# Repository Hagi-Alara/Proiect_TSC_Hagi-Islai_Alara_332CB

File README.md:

# InkTime - Open Source Smartwatch

Prezentul repository include documentația tehnică și fișierele de proiectare hardware (stadiul EVT - Engineering Verification Test) pentru proiectul InkTime. Acesta reprezintă un smartwatch open-source, având la bază microcontrolerul nRF52840. Proiectul acoperă întregul ciclu de dezvoltare hardware: specificații, schemă electrică, proiectare PCB și integrare mecanică.

## Descrierea Funcționalității Hardware

Sistemul este arhitecturat în jurul SoC-ului nRF52840, selectat pentru suportul Bluetooth Low Energy (BLE) și eficiența energetică ridicată.

**Module și Interfețe Integrate:**
* **Display E-Paper:** Interfațat prin protocolul SPI, garantând un consum energetic minim (curent absorbit exclusiv în timpul actualizării ecranului).
* **Unitate de Măsură Inerțială (IMU):** Utilizată pentru detectarea gesturilor. Comunicarea se realizează exclusiv prin magistrala I2C.
* **Feedback Haptic:** Motor de vibrații controlat printr-un circuit integrat (driver) dedicat, implementat pentru notificări.
* **Interfață Utilizator:** Trei butoane fizice cu acționare tactilă, configurate cu rezistențe de pull-up interne.
* **Managementul Energiei:** Sistemul este alimentat printr-un acumulator Li-Po conectat direct la pad-urile circuitului imprimat, eliminând conectorul JST pentru a respecta limitările de gabarit pe axa Z. Încărcarea se realizează prin intermediul interfeței USB-C, gestionată de un circuit integrat de management al puterii (PMIC), în timp ce nivelul de încărcare este monitorizat de un Fuel Gauge.

## Bill of Materials (BOM) Principal

| Componentă | Pachet / Capsulă | Funcție |
| :--- | :--- | :--- |
| **nRF52840-QIAA** | aQFN-73 | Microcontroler principal (SoC) + BLE |
| **BMA421** | LGA-12 | IMU (Accelerometru pentru gesturi) |
| **BQ25180** | DSBGA | PMIC (Management Încărcare Baterie) |
| **MAX17048** | TDFN-8 | Fuel Gauge (Monitorizare nivel baterie) |
| **DRV2605** | BGA-9 | Driver Haptic pentru motorul de vibrații |
| **RT6160A** | WLCSP | Regulator DC/DC (Buck-Boost pentru 3.3V) |
| **Conector Molex** | FPC 24-pin 0.5mm | Conector pentru Display E-Paper |

## Maparea Pinilor (nRF52840)

Alocarea pinilor a fost optimizată pentru a minimiza încrucișările de trasee pe cablajul imprimat.

| Pin nRF52840 | Nume Rețea | Interfață / Funcție |
| :--- | :--- | :--- |
| **P$AD10, P$K2, P$AD12** | `EPD_DC`, `EPD_CS`, `EPD_RST` | Control E-Paper (Data/Command, Chip Select, Reset) |
| **P$P13, P$A12** | `MOSI`, `SCK` | SPI Date & Clock pentru afișaj |
| **P$AD12** | `EPD_BUSY` | Status E-Paper (Indicator de ocupare) |
| **P$L1, P$M2** | `SDA`, `SCL` | I2C Date & Clock (PMIC, Fuel Gauge, IMU) |
| **P$AD8, P$AC9, P$W24** | `P0.13`, `P0.14`, `P1.02` | Butoane interfață utilizator (Up, Enter, Down) |
| **P$AD6, P$AD4, P$AD2**| `D+`, `D-`, `VBUS` | USB-C ESD Protection & VBUS Detect |
| **P$U1** | `HAPTIC_EN` | Semnal de activare Driver Haptic |
| **P$T2** | `PMIC_INT` | Întrerupere Baterie Li-Po |
| **P$N1, P$P2** | `IMU_INT1`, `IMU_INT2` | Întreruperi IMU |
| **P$J24** | `ALERT` | Alertă Fuel Gauge |
| **P$AD22, P$AA24, P$AC24** | `SWO`, `SWDCLK`, `SWDIO`| Interfață de depanare (SWD) |
| **P$AC13** | `RESET` | Semnal Hardware Reset |
| **P$Y23** | `P1.01` | Control E-Paper Drive Circuit |

## Randări 3D

## Etape de Implementare

1. **Definirea Specificațiilor și a Componentelor:** Selectarea componentelor necesare respectând cerința unui consum redus de energie (ultra-low-power).
2. **Proiectarea Schemei Electrice (Validare ERC):** Interconectarea subsistemelor de alimentare (PMIC, LDO), logică digitală (I2C, SPI) și radiofrecvență (RF).
3. **Proiectarea Cablajului Imprimat (Validare DRC):** * Amplasarea componentelor respectând constrângerile mecanice ale carcasei.
   * Rutarea traseelor de impedanță controlată pentru antena BLE, cu implementarea zonelor de restricție (Keepout) pe toate straturile.
   * Generarea planurilor de masă (Polygon Pours) pe straturile Top și Bottom.
4. **Validarea Mecanică:** Exportul ansamblului în format 3D STEP pentru verificarea toleranțelor de integrare în carcasa fizică.

## Erori de Proiectare (DRC/ERC) și Decizii de Inginerie Asumate

În urma procesului de verificare automată a regulilor de proiectare și a schemelor electrice (DRC/ERC), au fost raportate o serie de avertismente. Acestea au fost analizate și acceptate intenționat, având la bază următoarele justificări tehnice:

* **Erori ERC: "POWER pin connected to..." (Exemplu: U1 VDD connected to 3V3)**
  * *Justificare:* Aceste avertismente au fost ignorate. Cauza constă în definirea generică a pinilor de alimentare în biblioteca software (ex. "VDD"), în timp ce în schema proiectului rețeaua poartă o denumire specifică ("3V3" sau "VBAT"). Conexiunile sunt corecte din punct de vedere electric.
* **Erori ERC: "Only one pin on net" (Exemplu: SWO, SDA/1.4C, P1.15)**
  * *Justificare:* Aceste erori au fost ignorate. Avertismentele sunt generate deoarece pinii respectivi au fost rutați exclusiv către puncte de test (Test Points) pentru depanare sau au fost etichetați pentru funcționalități viitoare, nefiind conectați la un alt circuit integrat. Prezența lor este necesară pentru testarea hardware.
* **Erori DRC: "Overlap", "Solder mask", "Pad ct Top"**
  * *Justificare:* Aceste erori au fost acceptate. Având în vedere densitatea ridicată a plăcii, toleranțele măștii de lipire (Solder Mask) pentru componentele cu pas foarte mic (cum este conectorul FPC) se suprapun la nivelul software-ului CAD. Aceste deviații se încadrează în capabilitățile și toleranțele standard ale producătorului de cablaje imprimate.
* **Erori DRC: "Board Outline / Copper Clearance"**
  * *Justificare:* Aceste erori au fost acceptate. Erorile sunt provocate de componentele amplasate la limita cablajului (conectorul USB-C, contactele bateriei). Din rațiuni de asamblare mecanică, pinii de susținere și portul trebuie să se intersecteze cu conturul fizic al plăcii (Board Outline). Deși programul raportează o încălcare a regulilor de distanță, implementarea corespunde cerințelor fizice de funcționare.

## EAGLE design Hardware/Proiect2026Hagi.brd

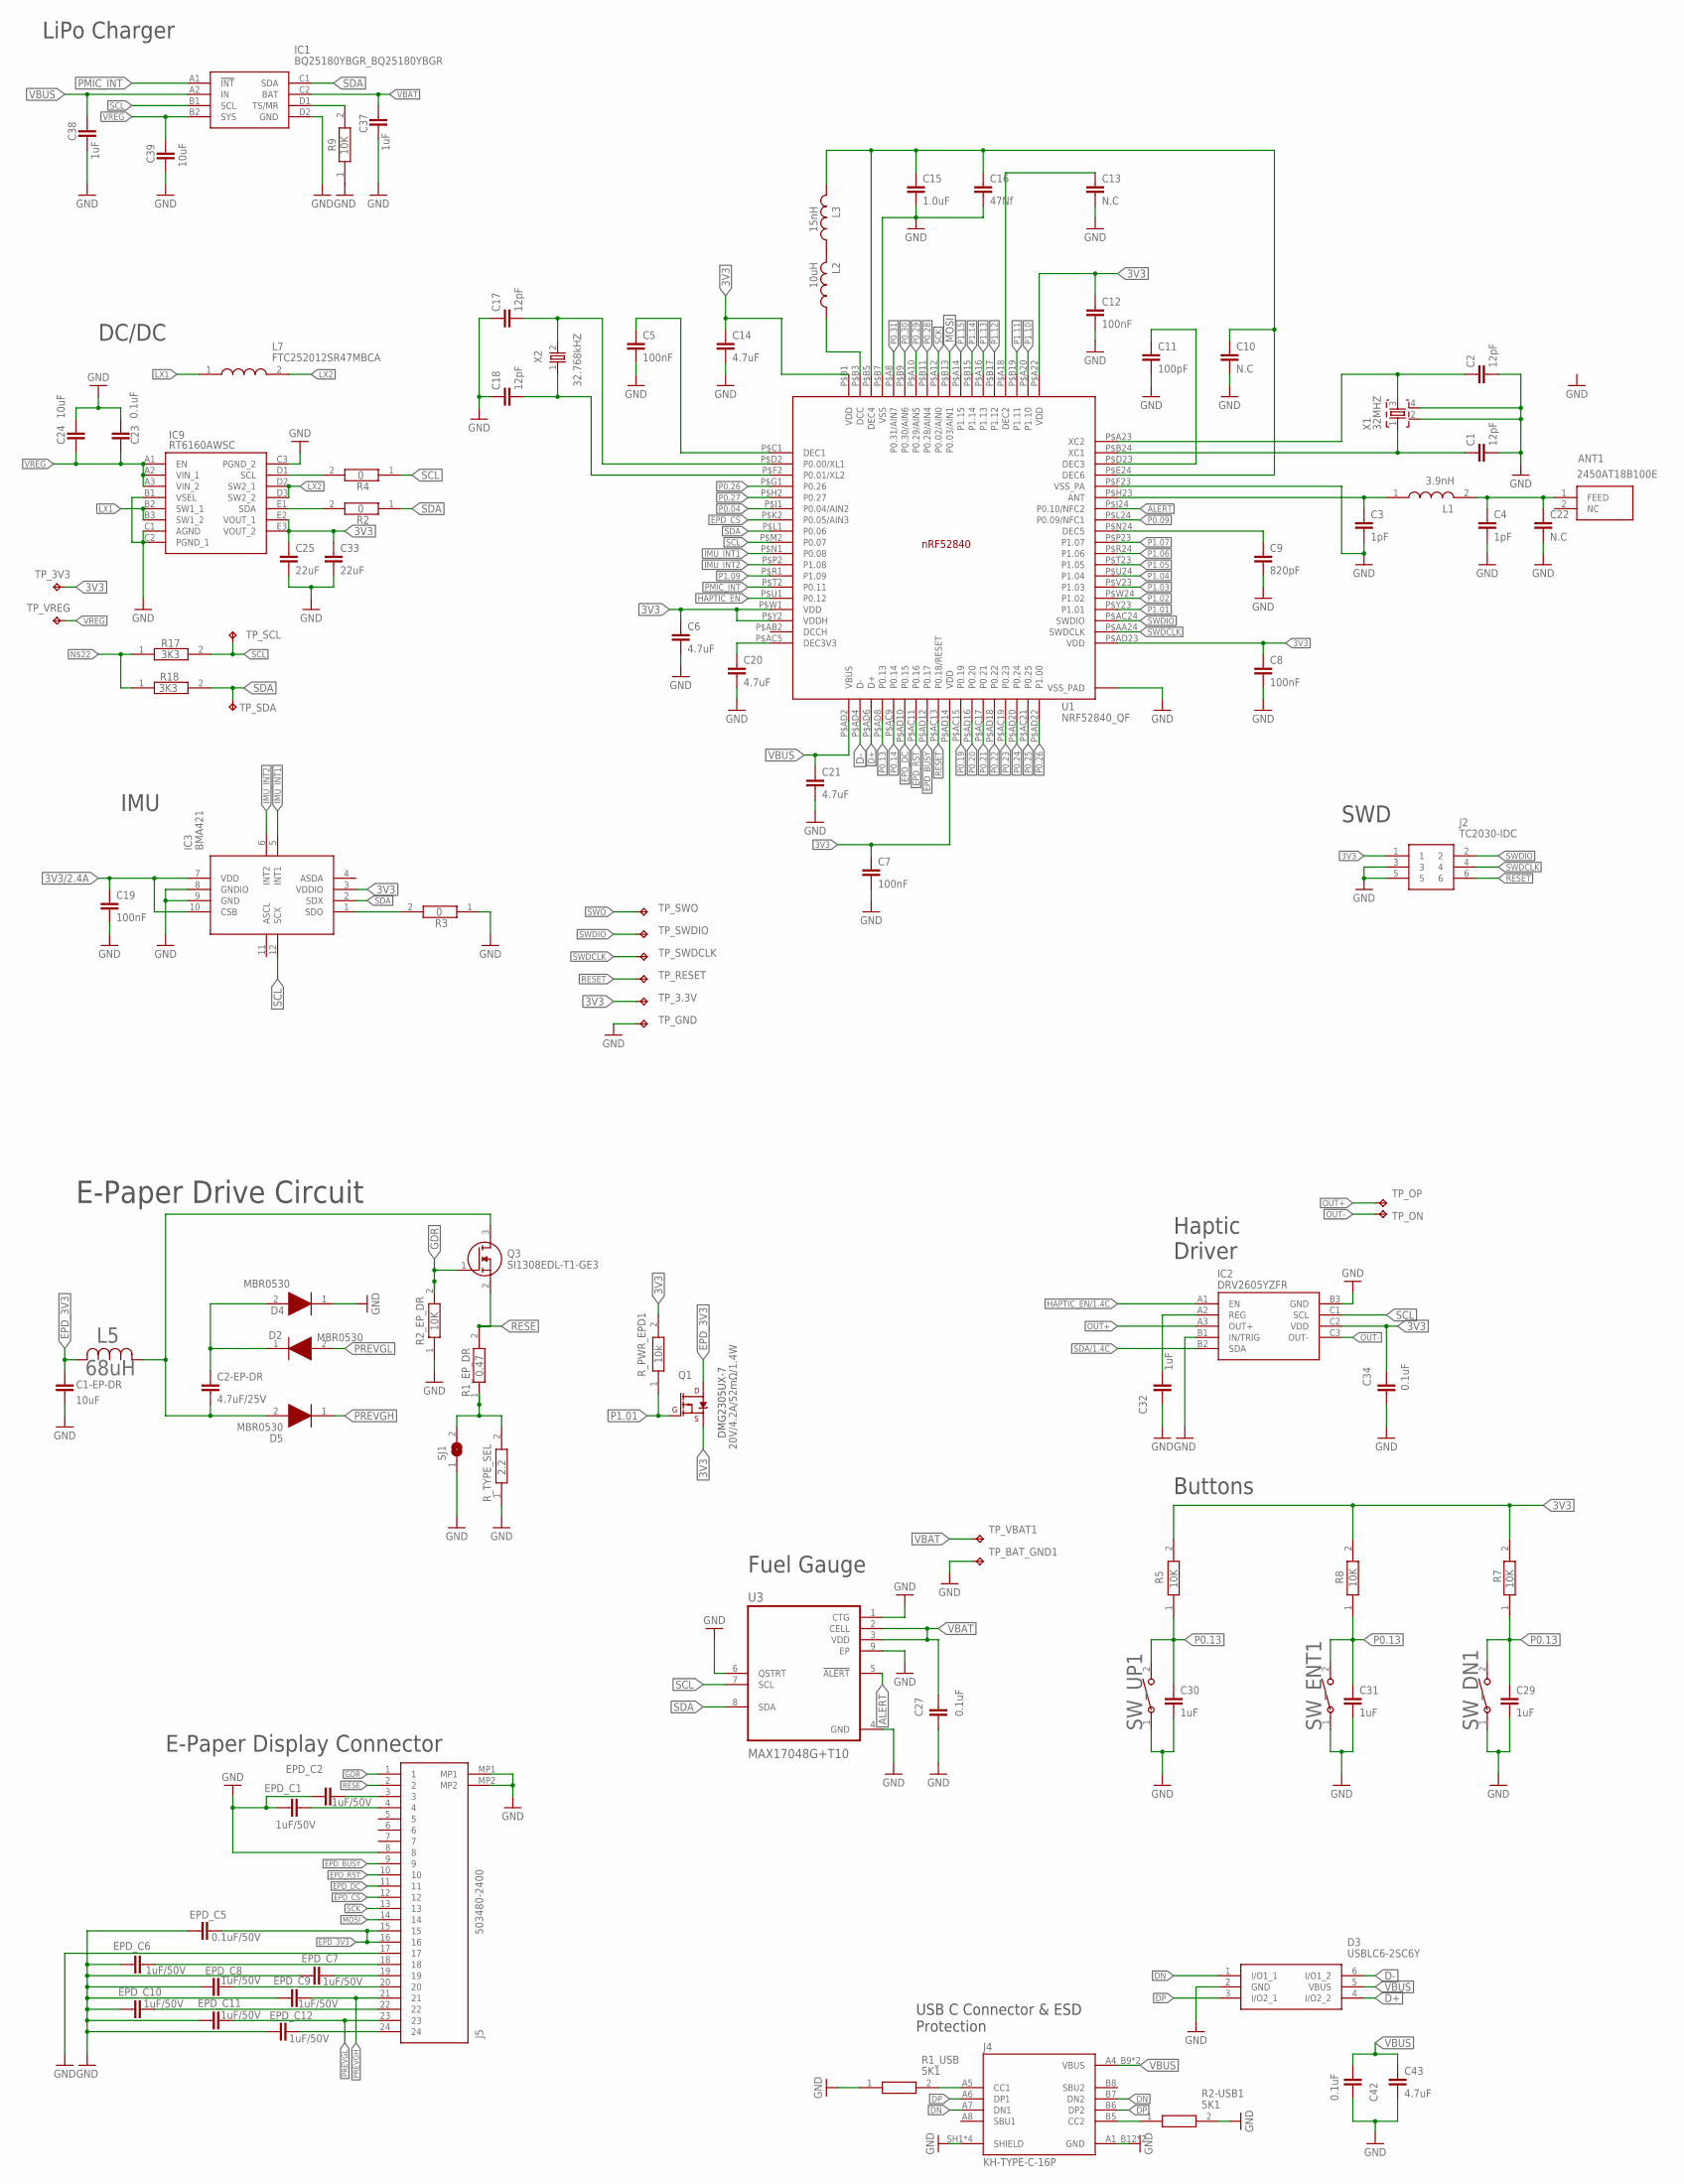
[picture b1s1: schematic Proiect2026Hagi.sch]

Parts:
ANT1: 2450AT18B100E; 2450AT18B100E_ANTC3216X140N
C1, C2, C17, C18: 12pF; NORDIC_NRF_3_RESC0201_L
C1-EP-DR: 10uF; NORDIC_NRF_3_RESC0402_L
C2-EP-DR: 4.7uF/25V; NORDIC_NRF_3_RESC0402_L
C3, C4: 1pF; NORDIC_NRF_3_RESC0201_L
C5, C7, C8, C12, C19: 100nF; NORDIC_NRF_3_RESC0201_L
C6, C14, C20, C21, C43: 4.7uF; NORDIC_NRF_3_RESC0402_L
C9: 820pF; NORDIC_NRF_3_RESC0201_L
C10, C13, C22: N.C; NORDIC_NRF_3_RESC0201_L
C11: 100pF; NORDIC_NRF_3_RESC0201_L
C15: 1.0uF; NORDIC_NRF_3_RESC0402_L
C16: 47Nf; NORDIC_NRF_3_RESC0201_L
C23: 0.1uF; NORDIC_NRF_3_RESC0402_L
C24: 10uF; NORDIC_NRF_3_RESC0201_L
C25, C33: 22uF; NORDIC_NRF_3_RESC0402_L
C27, C34, C42: 0.1uF; NORDIC_NRF_3_RESC0201_L
C29, C30, C31, C32: 1uF; NORDIC_NRF_3_RESC0402_L
C37, C38: 1uF; PERFECT_0402_0402
C39: 10uF; PERFECT_0402_0402
D2, D4, D5: MBR0530; ESP32_C6_LIBRARY_5_SOD3716X135N
D3: USBLC6-2SC6Y; ESP32_C6_LIBRARY_3_SOT95P280X145-6N
EPD_C1, EPD_C2, EPD_C6, EPD_C7, EPD_C8, EPD_C9, EPD_C10, EPD_C11, EPD_C12: 1uF/50V; NORDIC_NRF_3_RESC0402_L
EPD_C5: 0.1uF/50V; NORDIC_NRF_3_RESC0201_L
IC1: BQ25180YBGR_BQ25180YBGR; BQ25180YBGR_BGA8C40P2X4_100X155X50
IC2: DRV2605YZFR; DRV2605YZFR_BGA9C50P3X3_144X144X62
IC3: BMA421; BMA423_BMA423
IC9: RT6160AWSC; RT6160AWSC_BGA15C40P3X5_140X230X60
J2: TC2030-IDC; TC2030-IDC_TC2030IDC
J4: KH-TYPE-C-16P; KH-TYPE-C-16P_KINGHELM_KH-TYPE-C-16P
J5: 503480-2400; 503480-2400_5034802400
L1: 3.9nH; MLP2016SR47MT0S1_INDC2016X100N
L2: 10uH; NORDIC_NRF_2_RESC0402_L
L3: 15nH; NORDIC_NRF_2_RESC0402_L
L5: 68uH; ESP32_C6_LIBRARY_2_IND_4828-WE-TPC_WRE
L7: FTC252012SR47MBCA; MLP2016SR47MT0S1_INDC2016X100N
Q1: 20V/4.2A/52mΩ/1.4W; ESP32_C6_LIBRARY_4_ESP32_C6_LIBRARY_4_ESP32_C6_LIBRARY_4_ES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
Q3: SI1308EDL-T1-GE3; ESP32_C6_LIBRARY_6_SOT65P210X110-3N
R1_EP_DR: 0.47; CPF0201D7K68C1_0201
R1_USB, R2-USB1: 5K1; CPF0201D7K68C1_0201
R2, R3, R4: 0; CPF0201D7K68C1_0201
R2_EP_DR, R5, R7, R8, R9: 10K; CPF0201D7K68C1_0201
R17, R18: 3K3; CPF0201D7K68C1_0201
R_PWR_EPD1: 10k; CPF0201D7K68C1_0201
R_TYPE_SEL: 2.2; CPF0201D7K68C1_0201
SJ1: ESP32_C6_LIBRARY_7_JUMPER_SJ
SW_DN1: 2025-10-22_07-23-44_LIBRARY_EVP-AKE31ASW_EVP-AKE3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; 2025-10-22_07-23-44_LIBRARY_SW_EVP-AKE31A_PAN
SW_ENT1: 2025-10-22_07-23-44_LIBRARY_EVP-AKE31ASW_EVP-AKE3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; 2025-10-22_07-23-44_LIBRARY_SW_EVP-AKE31A_PAN
SW_UP1: 2025-10-22_07-23-44_LIBRARY_EVP-AKE31ASW_EVP-AKE3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; 2025-10-22_07-23-44_LIBRARY_SW_EVP-AKE31A_PAN
TP_3.3V, TP_3V3: HECTOR_WATCH_1_TPTP20R; HECTOR_WATCH_1_TP20R
TP_BAT_GND1: HECTOR_WATCH_1_TPTP20R; HECTOR_WATCH_1_TP20R
TP_GND: HECTOR_WATCH_1_TPTP20R; HECTOR_WATCH_1_TP20R
TP_ON: HECTOR_WATCH_1_TPTP20R; HECTOR_WATCH_1_TP20R
TP_OP: HECTOR_WATCH_1_TPTP20R; HECTOR_WATCH_1_TP20R
TP_RESET: HECTOR_WATCH_1_TPTP20R; HECTOR_WATCH_1_TP20R
TP_SCL: HECTOR_WATCH_1_TPTP20R; HECTOR_WATCH_1_TP20R
TP_SDA: HECTOR_WATCH_1_TPTP20R; HECTOR_WATCH_1_TP20R
TP_SWDCLK: HECTOR_WATCH_1_TPTP20R; HECTOR_WATCH_1_TP20R
TP_SWDIO: HECTOR_WATCH_1_TPTP20R; HECTOR_WATCH_1_TP20R
TP_SWO: HECTOR_WATCH_1_TPTP20R; HECTOR_WATCH_1_TP20R
TP_VBAT1: HECTOR_WATCH_1_TPTP20R; HECTOR_WATCH_1_TP20R
TP_VREG: HECTOR_WATCH_1_TPTP20R; HECTOR_WATCH_1_TP20R
U1: NRF52840_QF; NORDIC_NRF_4_AQFN50P700X700X85_HS-74N
U3: MAX17048G+T10; ESP32_C6_LIBRARY_SON50P200X200X80-9N
X1: 32MHZ; NORDIC_NRF_BT-XTAL_2016_N
X2: 32.768kHZ; NORDIC_NRF_1_XTAL_3215_N

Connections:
3V3: C6.1, C7.1, C8.1, C12.1, C14.1, C25.1, C33.1, C34.1, IC2.C2 (VDD), IC3.3 (VDDIO), IC9.E2 (VOUT_1), IC9.E3 (VOUT_2), J2.1, Q1.2 (S), R5.2, R7.2, R8.2, R_PWR_EPD1.2, TP_3.3V.TP, TP_3V3.TP, U1.P$A22 (VDD), U1.P$AD14 (VDD), U1.P$AD23 (VDD), U1.P$B1 (VDD), U1.P$W1 (VDD), U1.P$Y2 (VDDH)
3V3/2.4A: C19.1, IC3.7 (VDD), IC3.10 (CSB)
ALERT: U1.P$J24 (P0.10/NFC2), U3.5 (!ALERT)
D+: D3.4 (I/O2_2), U1.P$AD6 (D+)
D-: D3.6 (I/O1_2), U1.P$AD4 (D-)
DN: D3.1 (I/O1_1), J4.A7 (DN1), J4.B7 (DN2)
DP: D3.3 (I/O2_1), J4.A6 (DP1), J4.B6 (DP2)
EPD_3V3: C1-EP-DR.1, EPD_C5.2, J5.15, J5.16, L5.2, Q1.3 (D)
EPD_BUSY: J5.9, U1.P$AD12 (P0.17)
EPD_CS: J5.12, U1.P$K2 (P0.05/AIN3)
EPD_DC: J5.11, U1.P$AD10 (P0.15)
EPD_RST: J5.10, U1.P$AC11 (P0.16)
GDR: J5.1, Q3.1 (G), R2_EP_DR.2
GND: C1.2, C1-EP-DR.2, C2.2, C3.2, C4.2, C5.2, C6.2, C7.2, C8.2, C9.2, C10.2, C11.2, C12.2, C13.2, C14.2, C15.2, C16.2, C17.1, C18.1, C19.2, C20.2, C21.2, C22.2, C23.1, C24.1, C25.2, C27.2, C29.2, C30.2, C31.2, C32.2, C33.2, C34.2, C37.2, C38.2, C39.2, C42.2, C43.2, D3.2 (GND), D4.1 (K), EPD_C1.1, EPD_C2.1, EPD_C5.1, EPD_C6.1, EPD_C7.1, EPD_C8.1, EPD_C9.1, EPD_C10.1, EPD_C11.1, EPD_C12.1, IC1.D2 (GND), IC2.B1 (IN/TRIG), IC2.B3 (GND), IC3.8 (GNDIO), IC3.9 (GND), IC9.B1 (VSEL), IC9.C1 (AGND), IC9.C2 (PGND_1), IC9.C3 (PGND_2), J2.3, J2.5, J4.A1_B12 (GND), J4.A12_B1 (GND), J4.SH1 (SHIELD), J4.SH2 (SHIELD), J4.SH3 (SHIELD), J4.SH4 (SHIELD), J5.8, J5.17, J5.MP1, J5.MP2, R1_USB.1, R2-USB1.2, R2_EP_DR.1, R3.1, R9.1, R_TYPE_SEL.1, SJ1.1, SW_DN1.1, SW_ENT1.1, SW_UP1.1, TP_BAT_GND1.TP, TP_GND.TP, U1.P$74 (VSS_PAD), U1.P$75 (VSS_PAD), U1.P$76 (VSS_PAD), U1.P$77 (VSS_PAD), U1.P$78 (VSS_PAD), U1.P$79 (VSS_PAD), U1.P$80 (VSS_PAD), U1.P$81 (VSS_PAD), U1.P$82 (VSS_PAD), U1.P$83 (VSS_PAD), U1.P$84 (VSS_PAD), U1.P$85 (VSS_PAD), U1.P$86 (VSS_PAD), U1.P$87 (VSS_PAD), U1.P$88 (VSS_PAD), U1.P$89 (VSS_PAD), U1.P$90 (VSS_PAD), U1.P$B7 (VSS), U1.P$F23 (VSS_PA), U3.1 (CTG), U3.4 (GND), U3.6 (QSTRT), U3.9 (EP), X1.2, X1.4
HAPTIC_EN: U1.P$U1 (P0.12)
HAPTIC_EN/1.4C: IC2.A1 (EN)
IMU_INT1: IC3.5 (INT1), U1.P$N1 (P0.08)
IMU_INT2: IC3.6 (INT2), U1.P$P2 (P1.08)
LX1: IC9.B2 (SW1_1), IC9.B3 (SW1_2), L7.1
LX2: IC9.D2 (SW2_1), IC9.D3 (SW2_2), L7.2
MOSI: J5.14, U1.P$B13 (P0.03/AIN1)
unnamed: IC9.D1 (SCL), R4.2
unnamed: C5.1, U1.P$C1 (DEC1)
unnamed: C9.1, U1.P$N24 (DEC5)
unnamed: C20.1, U1.P$AC5 (DEC3V3)
unnamed: C11.1, U1.P$D23 (DEC3)
unnamed: IC9.E1 (SDA), R2.2
unnamed: IC1.D1 (TS/MR), R9.2
unnamed: J4.A5 (CC1), R1_USB.2
unnamed: IC3.1 (SDO), R3.2
unnamed: L2.1, U1.P$B3 (DCC)
unnamed: C10.1, C15.1, C16.1, L3.2, U1.P$B5 (DEC4), U1.P$E24 (DEC6)
unnamed: C3.1, L1.1, U1.P$H23 (ANT)
unnamed: ANT1.1 (FEED), C4.1, C22.1, L1.2
unnamed: C1.1, U1.P$B24 (XC1), X1.1
unnamed: C2.1, U1.P$A23 (XC2), X1.3
unnamed: C17.2, U1.P$D2 (P0.00/XL1), X2.2
unnamed: C18.2, U1.P$F2 (P0.01/XL2), X2.1
unnamed: L2.2, L3.1
unnamed: R17.1, R18.1
unnamed: C13.1, U1.P$A18 (DEC2)
unnamed: J4.B5 (CC2), R2-USB1.1
unnamed: C32.1, IC2.A2 (REG)
unnamed: EPD_C2.2, J5.3
unnamed: EPD_C1.2, J5.4
unnamed: EPD_C6.2, J5.18
unnamed: EPD_C7.2, J5.19
unnamed: EPD_C8.2, J5.20
unnamed: EPD_C10.2, J5.22
unnamed: EPD_C12.2, J5.24
unnamed: C2-EP-DR.2, D5.2 (A), L5.1, Q3.3 (D)
unnamed: C2-EP-DR.1, D2.1 (K), D4.2 (A)
unnamed: R1_EP_DR.1, R_TYPE_SEL.2, SJ1.2
OUT+: IC2.A3 (OUT+), TP_OP.TP
OUT-: IC2.C3 (OUT-), TP_ON.TP
P0.04: U1.P$J1 (P0.04/AIN2)
P0.09: U1.P$L24 (P0.09/NFC1)
P0.13: C29.1, C30.1, C31.1, R5.1, R7.1, R8.1, SW_DN1.2, SW_ENT1.2, SW_UP1.2, U1.P$AD8 (P0.13)
P0.14: U1.P$AC9 (P0.14)
P0.19: U1.P$AC15 (P0.19)
P0.20: U1.P$AD16 (P0.20)
P0.21: U1.P$AC17 (P0.21)
P0.22: U1.P$AD18 (P0.22)
P0.23: U1.P$AC19 (P0.23)
P0.24: U1.P$AD20 (P0.24)
P0.25: U1.P$AC21 (P0.25)
P0.26: U1.P$AD22 (P1.00), U1.P$G1 (P0.26)
P0.27: U1.P$H2 (P0.27)
P0.28: U1.P$B11 (P0.28/AIN4)
P0.29: U1.P$A10 (P0.29/AIN5)
P0.30: U1.P$B9 (P0.30/AIN6)
P0.31: U1.P$A8 (P0.31/AIN7)
P1.01: Q1.1 (G), R_PWR_EPD1.1, U1.P$Y23 (P1.01)
P1.02: U1.P$W24 (P1.02)
P1.03: U1.P$V23 (P1.03)
P1.04: U1.P$U24 (P1.04)
P1.05: U1.P$T23 (P1.05)
P1.06: U1.P$R24 (P1.06)
P1.07: U1.P$P23 (P1.07)
P1.09: U1.P$R1 (P1.09)
P1.10: U1.P$A20 (P1.10)
P1.11: U1.P$B19 (P1.11)
P1.12: U1.P$B17 (P1.12)
P1.13: U1.P$A16 (P1.13)
P1.14: U1.P$B15 (P1.14)
P1.15: U1.P$A14 (P1.15)
PMIC_INT: IC1.A1 (!INT), U1.P$T2 (P0.11)
PREVGH: D5.1 (K), EPD_C9.2, J5.21
PREVGL: D2.2 (A), EPD_C11.2, J5.23
RESE: J5.2, Q3.2 (S), R1_EP_DR.2
RESET: J2.6, TP_RESET.TP, U1.P$AC13 (P0.18/RESET)
SCK: J5.13, U1.P$A12 (P0.02/AIN0)
SCL: IC1.B1 (SCL), IC2.C1 (SCL), IC3.12 (SCX), R4.1, R17.2, TP_SCL.TP, U1.P$M2 (P0.07), U3.7 (SCL)
SDA: IC1.C1 (SDA), IC3.2 (SDX), R2.1, R18.2, TP_SDA.TP, U1.P$L1 (P0.06), U3.8 (SDA)
SDA/1.4C: IC2.B2 (SDA)
SWDCLK: J2.4, TP_SWDCLK.TP, U1.P$AA24 (SWDCLK)
SWDIO: J2.2, TP_SWDIO.TP, U1.P$AC24 (SWDIO)
SWO: TP_SWO.TP
VBAT: C27.1, C37.1, IC1.C2 (BAT), TP_VBAT1.TP, U3.2 (CELL), U3.3 (VDD)
VBUS: C21.1, C38.1, C42.1, C43.1, D3.5 (VBUS), IC1.A2 (IN), J4.A4_B9 (VBUS), J4.A9_B4 (VBUS), U1.P$AD2 (VBUS)
VREG: C23.2, C24.2, C39.1, IC1.B2 (SYS), IC9.A1 (EN), IC9.A2 (VIN_1), IC9.A3 (VIN_2), TP_VREG.TP

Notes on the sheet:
IMU
DC/DC
LiPo Charger
SWD
USB C Connector & ESD Protection
E-Paper Display Connector
E-Paper Drive Circuit
DMG2305UX-7
Haptic Driver
Buttons
Fuel Gauge

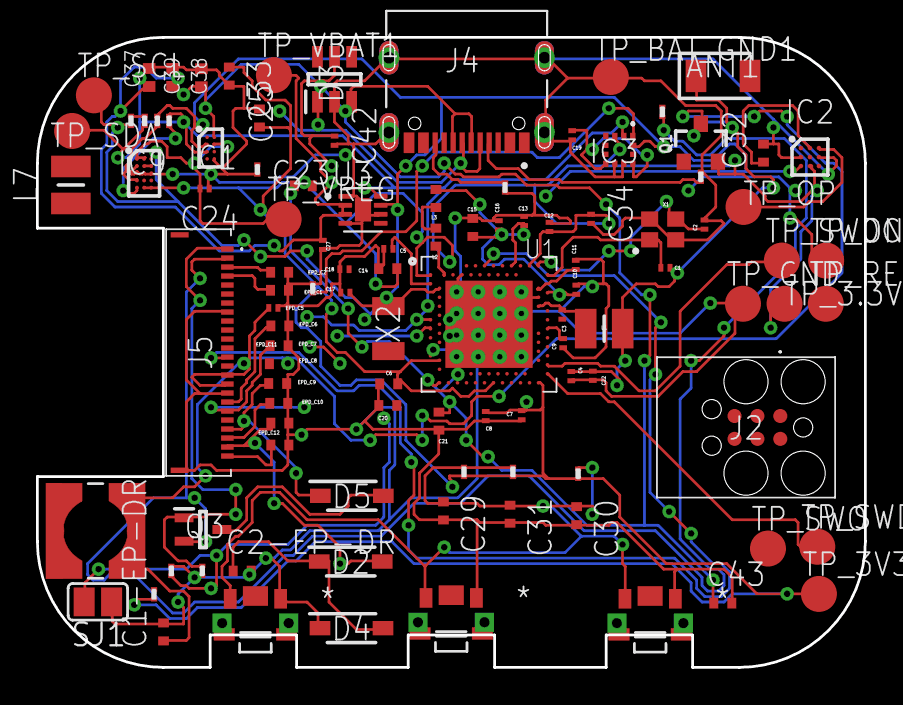
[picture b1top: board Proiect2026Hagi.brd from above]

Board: 4 copper layers, 46.0 x 35.0 mm, 105 parts (0 on the bottom side), 69 nets.

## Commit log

2026-04-22 Update README to remove BOM note
    Removed note about BOM table reflecting major components.
2026-04-22 Update LICENSE

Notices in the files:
parts and their libraries:
COPYRIGHT: Copyright (C) 2024 Ultra Librarian. All rights reserved.
COPYRIGHT: Copyright (C) 2025 Ultra Librarian. All rights reserved.
